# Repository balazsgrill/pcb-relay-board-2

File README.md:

# pcb-relay-board-2
Printed Circuit Board for 5V Relays x8

## Bill of Materials

* Compatible relays: 5V coil / 230V-10A
  * Songle SRD-5VDC-SL-C
  * Zetter AZ943-1CH-5DE 
  * Hongfa HF3FA/005-ZT
  * Omron G5LE-1
  * Panasonic JS1-5V-F
* Transistors: BC337 or compatible (CBE layout)
* Diodes: 1N4148 or similar
* Resistors: 5K
* Capacitor: 100uF

## J1 connector pinout
| Function | Pin | Pin | Function |
| --- | --- | --- | --- |
| 5V | 1 | 2  | Relay 0  |
| Relay 1 | 3 | 4  | Relay 2  |
| Relay 3 | 5 | 6  | Relay 7  |
| Relay 4 | 7 | 8  | Relay 5  |
| Relay 5 | 9 | 10 | GND  |

## Errata

* On the silscreen, Normally on and Normally off indications (NONx and NOFFx respectively are reversed)

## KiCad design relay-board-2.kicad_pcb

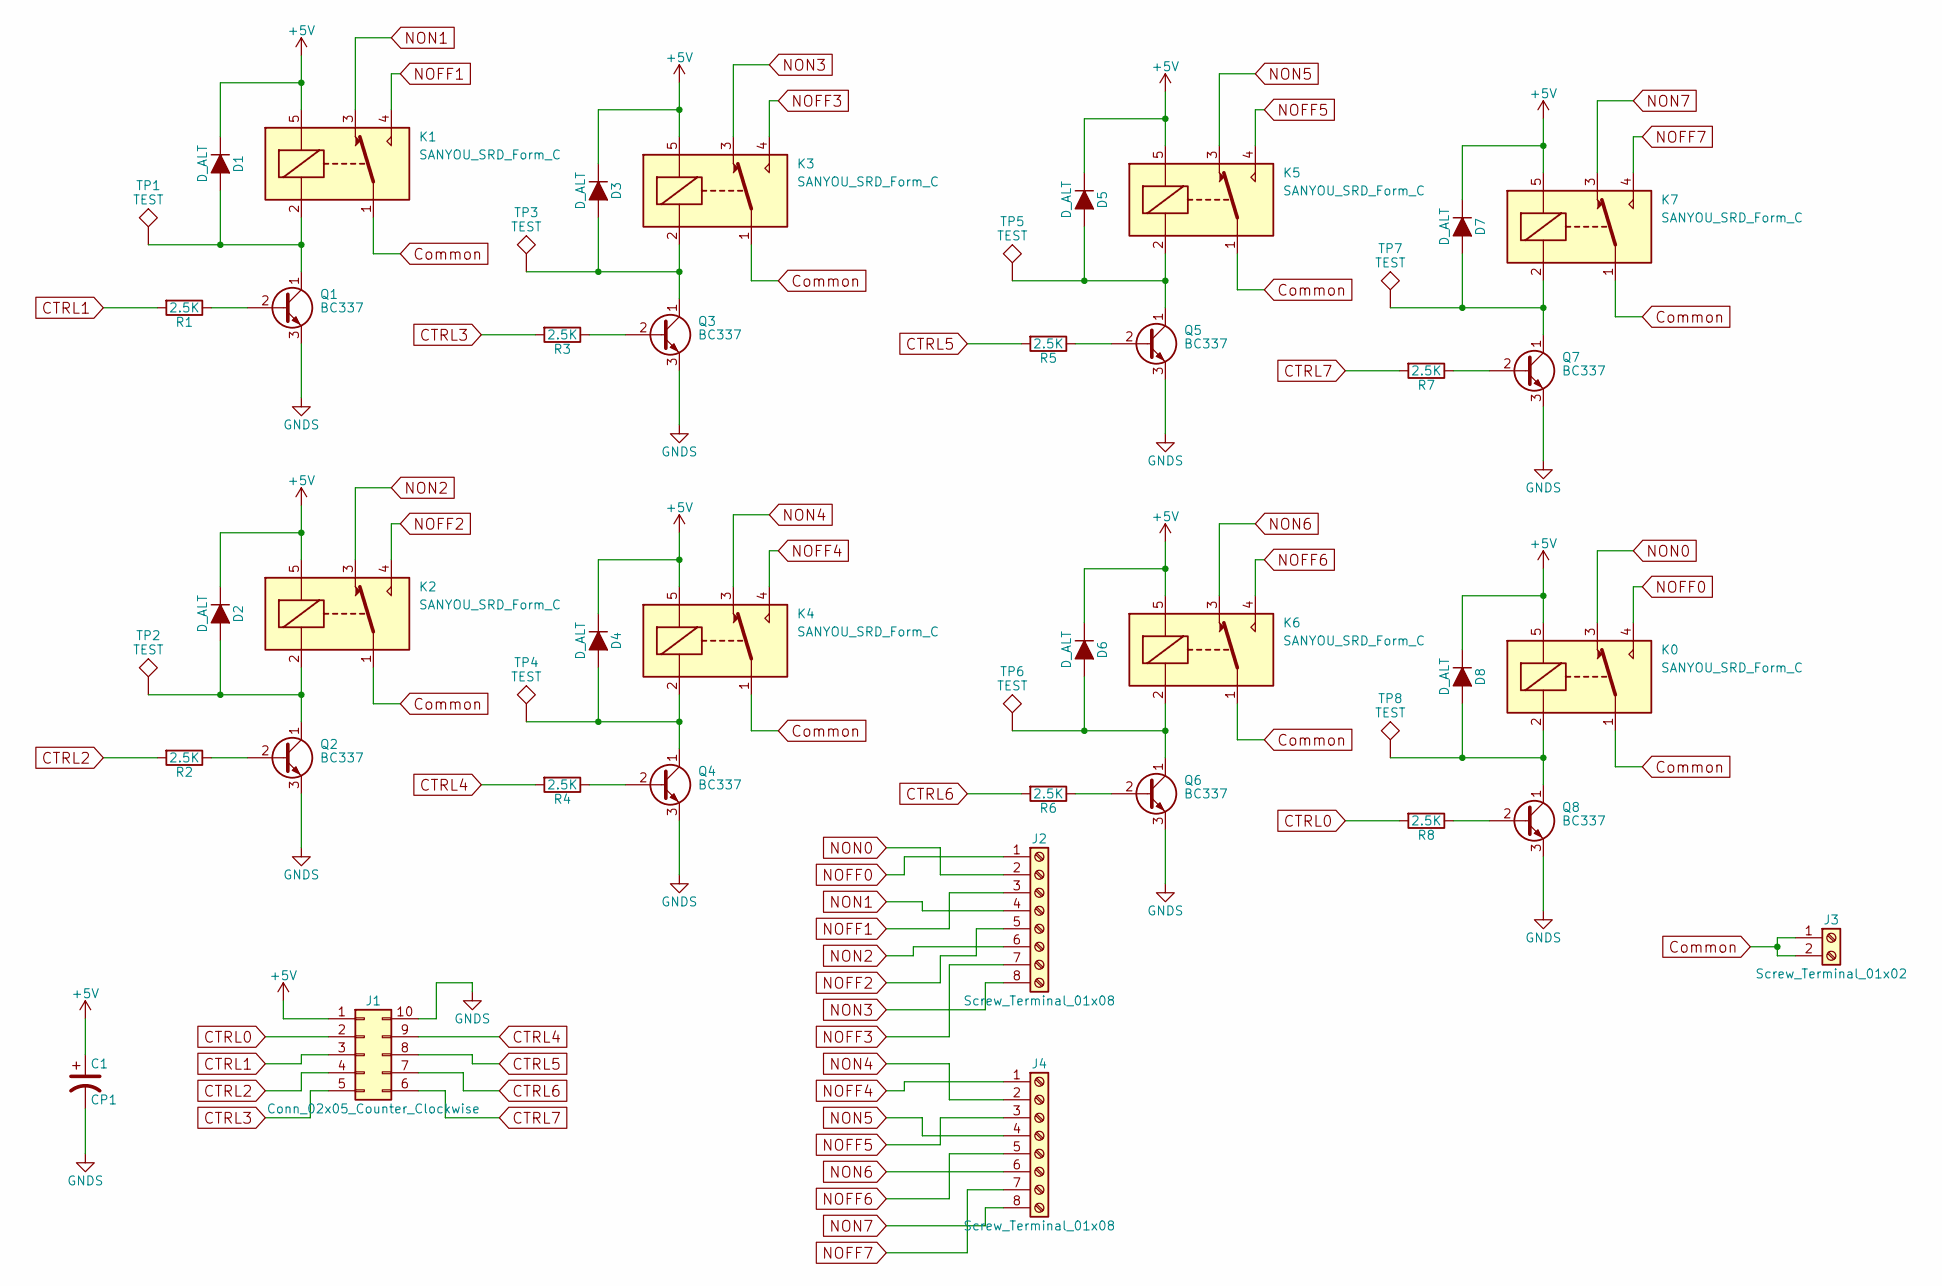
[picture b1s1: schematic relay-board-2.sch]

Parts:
C1: CP1; CP_Radial_D8.0mm_P3.50mm
D1, D2, D3, D4, D5, D6, D7, D8: D_ALT; D_A-405_P7.62mm_Horizontal
J1: Conn_02x05_Counter_Clockwise; Pin_Header_Straight_2x05_Pitch2.54mm
J2, J4: Screw_Terminal_01x08; TerminalBlock_Phoenix_PT-3.5mm_8pol
J3: Screw_Terminal_01x02; TerminalBlock_Phoenix_PT-3.5mm_2pol
K0, K1, K2, K3, K4, K5, K6, K7: SANYOU_SRD_Form_C; Relay_SPDT_SANYOU_SRD_Series_Form_C
Q1, Q2, Q3, Q4, Q5, Q6, Q7, Q8: BC337; TO-92_Inline_Wide
R1, R2, R3, R4, R5, R6, R7, R8: 2.5K; R_Axial_DIN0204_L3.6mm_D1.6mm_P5.08mm_Horizontal
TP1, TP2, TP3, TP4, TP5, TP6, TP7, TP8: TEST; Pin_Header_Straight_1x01_Pitch1.00mm

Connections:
+5V: C1.1, D1.1 (K), D2.1 (K), D3.1 (K), D4.1 (K), D5.1 (K), D6.1 (K), D7.1 (K), D8.1 (K), J1.1, K0.5, K1.5, K2.5, K3.5, K4.5, K5.5, K6.5, K7.5
CTRL0: J1.2, R8.2
CTRL1: J1.3, R1.2
CTRL2: J1.4, R2.2
CTRL3: J1.5, R3.2
CTRL4: J1.9, R4.2
CTRL5: J1.8, R5.2
CTRL6: J1.7, R6.2
CTRL7: J1.6, R7.2
Common: J3.1, J3.2, K0.1, K1.1, K2.1, K3.1, K4.1, K5.1, K6.1, K7.1
GNDS: C1.2, J1.10, Q1.3 (E), Q2.3 (E), Q3.3 (E), Q4.3 (E), Q5.3 (E), Q6.3 (E), Q7.3 (E), Q8.3 (E)
NOFF0: J2.1, K0.4
NOFF1: J2.3, K1.4
NOFF2: J2.5, K2.4
NOFF3: J2.7, K3.4
NOFF4: J4.1, K4.4
NOFF5: J4.3, K5.4
NOFF6: J4.5, K6.4
NOFF7: J4.7, K7.4
NON0: J2.2, K0.3
NON1: J2.4, K1.3
NON2: J2.6, K2.3
NON3: J2.8, K3.3
NON4: J4.2, K4.3
NON5: J4.4, K5.3
NON6: J4.6, K6.3
NON7: J4.8, K7.3
unnamed: D1.2 (A), K1.2, Q1.1 (C), TP1.1
unnamed: D2.2 (A), K2.2, Q2.1 (C), TP2.1
unnamed: D3.2 (A), K3.2, Q3.1 (C), TP3.1
unnamed: D4.2 (A), K4.2, Q4.1 (C), TP4.1
unnamed: D5.2 (A), K5.2, Q5.1 (C), TP5.1
unnamed: D6.2 (A), K6.2, Q6.1 (C), TP6.1
unnamed: D7.2 (A), K7.2, Q7.1 (C), TP7.1
unnamed: D8.2 (A), K0.2, Q8.1 (C), TP8.1
unnamed: Q1.2 (B), R1.1
unnamed: Q2.2 (B), R2.1
unnamed: Q3.2 (B), R3.1
unnamed: Q4.2 (B), R4.1
unnamed: Q5.2 (B), R5.1
unnamed: Q6.2 (B), R6.1
unnamed: Q7.2 (B), R7.1
unnamed: Q8.2 (B), R8.1

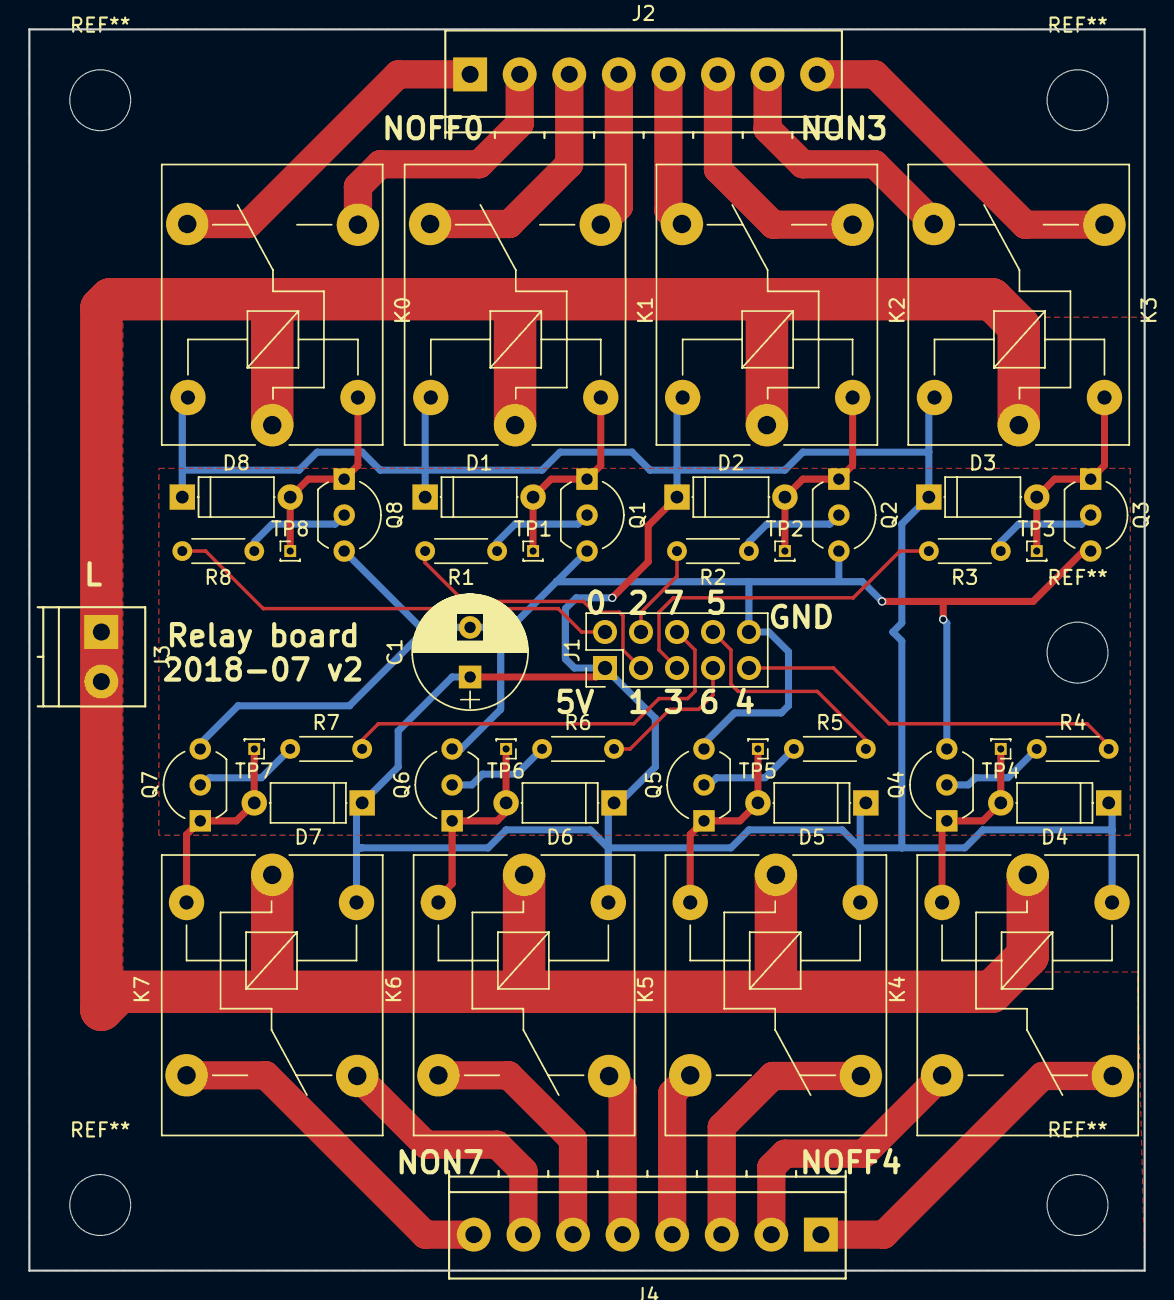
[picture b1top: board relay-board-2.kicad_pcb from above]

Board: 2 copper layers, 78.7 x 87.6 mm, 45 parts (0 on the bottom side), 43 nets.

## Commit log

2019-12-19 Initial publish of design
